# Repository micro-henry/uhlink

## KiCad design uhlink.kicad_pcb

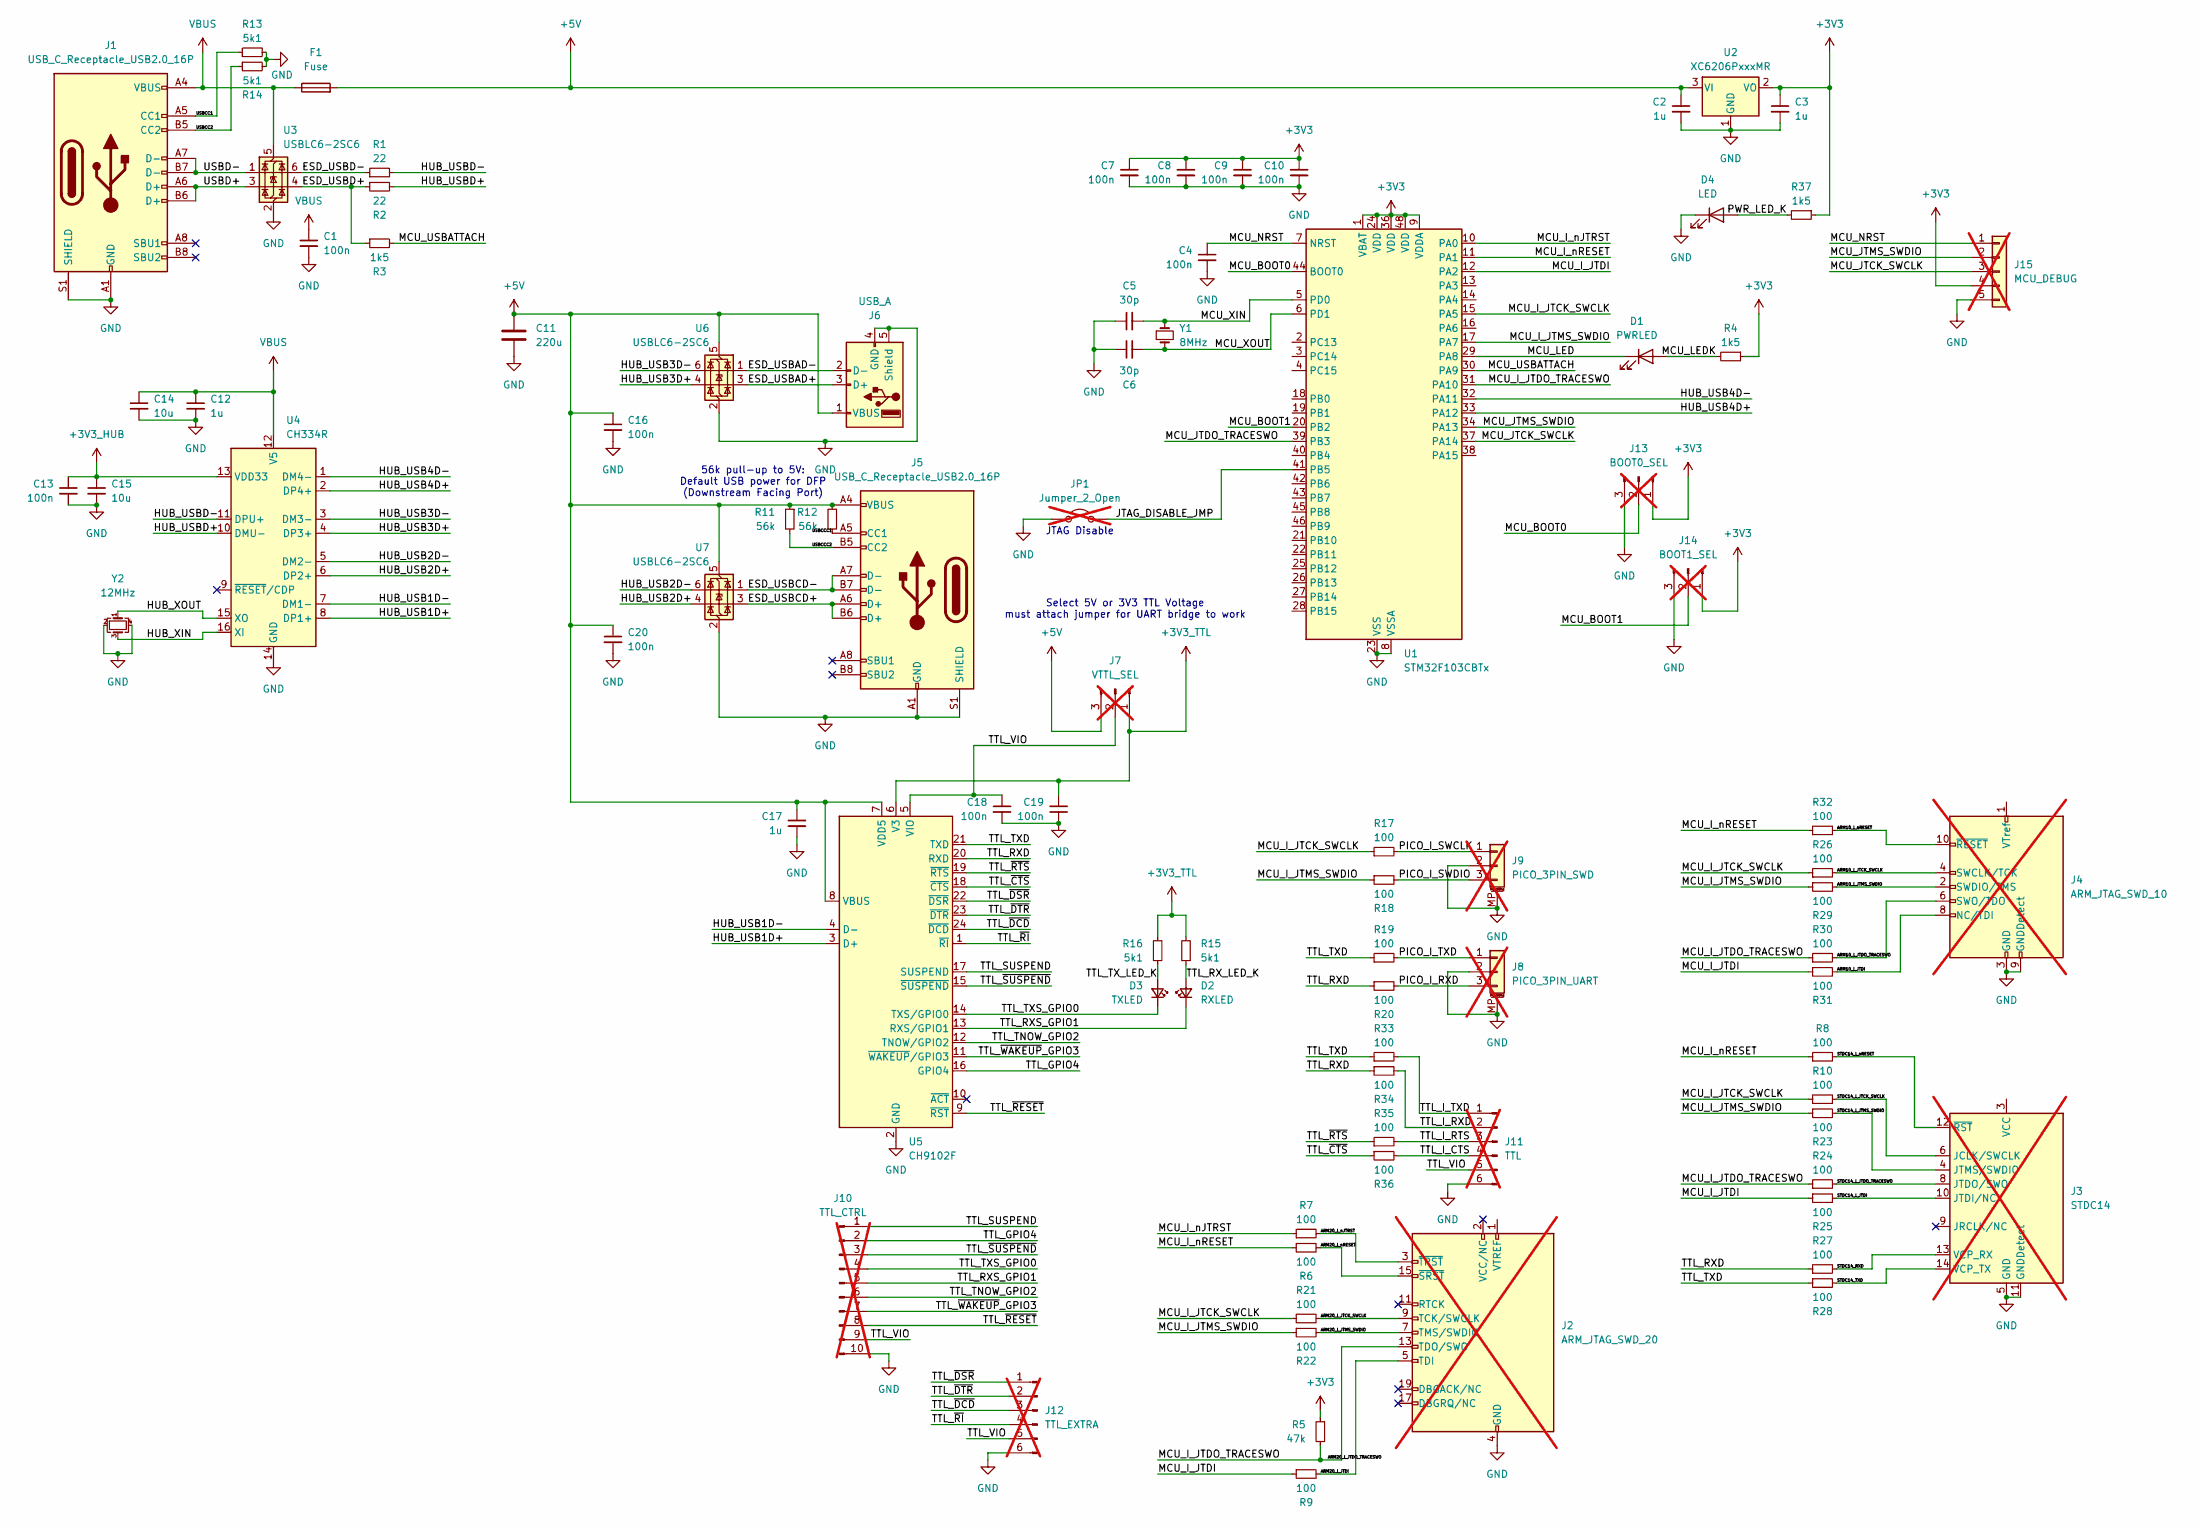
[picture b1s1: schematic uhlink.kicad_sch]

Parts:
C1, C4, C7, C8, C9, C10, C13, C16, C18, C19, C20: 100n; C_0402_1005Metric; LCSC C1525
C2, C3, C12, C17: 1u; C_0402_1005Metric; LCSC C52923
C5, C6: 30p; C_0402_1005Metric; LCSC C1570
C11: 220u; C_Radial_D10.0mm_H16.0mm_P5.00mm; LCSC C2873996
C14, C15: 10u; C_0402_1005Metric; LCSC C15525
D1: PWRLED; LED_0805_2012Metric; LCSC C84256
D2: RXLED; LED_0805_2012Metric; LCSC C2296
D3: TXLED; LED_0805_2012Metric; LCSC C2297
D4: LED; LED_0805_2012Metric; LCSC C2297
F1: Fuse
J1, J5: USB_C_Receptacle_USB2.0_16P; USB_C_Receptacle_HRO_TYPE-C-31-M-12; LCSC C2765186
J2: ARM_JTAG_SWD_20; IDC-Header_2x10_P2.54mm_Vertical; not fitted
J3: STDC14; PinHeader_2x07_P1.27mm_Vertical; not fitted
J4: ARM_JTAG_SWD_10; PinHeader_2x05_P1.27mm_Vertical; not fitted
J6: USB_A; USB_A_Receptacle_GCT_USB1046
J7: VTTL_SEL; PinHeader_1x03_P2.54mm_Vertical; not fitted
J8: PICO_3PIN_UART; JST_SH_BM03B-SRSS-TB_1x03-1MP_P1.00mm_Vertical; not fitted
J9: PICO_3PIN_SWD; JST_SH_BM03B-SRSS-TB_1x03-1MP_P1.00mm_Vertical; not fitted
J10: TTL_CTRL; PinHeader_1x10_P2.54mm_Vertical; not fitted
J11: TTL; PinHeader_1x06_P2.54mm_Vertical; not fitted
J12: TTL_EXTRA; PinHeader_1x06_P2.54mm_Vertical; not fitted
J13: BOOT0_SEL; PinHeader_1x03_P2.54mm_Vertical; not fitted
J14: BOOT1_SEL; PinHeader_1x03_P2.54mm_Vertical; not fitted
J15: MCU_DEBUG; PinHeader_1x05_P2.00mm_Vertical; not fitted
JP1: Jumper_2_Open; TestPoint_2Pads_Pitch2.54mm_Drill0.8mm; not fitted
R1, R2: 22; R_0402_1005Metric; LCSC C25092
R3, R4, R37: 1k5; R_0402_1005Metric; LCSC C25867
R5: 47k; R_0402_1005Metric; LCSC C25792
R6, R7, R8, R9, R10, R17, R18, R19, R20, R21, R22, R23, R24, R25, R26, R27, R28, R29, R30, R31, R32, R33, R34, R35, R36: 100; R_0402_1005Metric; LCSC C25076
R11, R12: 56k; R_0603_1608Metric; LCSC C23206
R13, R14, R15, R16: 5k1; R_0402_1005Metric; LCSC C25905
U1: STM32F103CBTx; LQFP-48_7x7mm_P0.5mm; LCSC C8304
U2: XC6206PxxxMR; SOT-23-3; LCSC C5446
U3, U6, U7: USBLC6-2SC6; SOT-23-6; LCSC C7519
U4: CH334R; QSOP-16_3.9x4.9mm_P0.635mm; LCSC C4154405
U5: CH9102F; QFN-24-1EP_4x4mm_P0.5mm_EP2.6x2.6mm; LCSC C2858418
Y1: 8MHz; Crystal_SMD_HC49-SD; LCSC C12674
Y2: 12MHz; Crystal_SMD_3225-4Pin_3.2x2.5mm; LCSC C9002

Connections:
+3V3: C3.1, C7.1, C8.1, C9.1, C10.1, J13.1, J14.1, J15.4, R4.1, R5.1, R37.1, U1.1 (VBAT), U1.9 (VDDA), U1.24 (VDD), U1.36 (VDD), U1.48 (VDD), U2.2 (VO)
+3V3_HUB: C13.1, C15.1, U4.13 (VDD33)
+3V3_TTL: C19.1, J7.1, R15.2, R16.2, U5.6 (V3)
+5V: C2.1, C11.1, C16.1, C17.1, C20.1, F1.2, J5.A4 (VBUS), J5.A9 (VBUS), J5.B4 (VBUS), J5.B9 (VBUS), J6.1 (VBUS), J7.3, R11.1, R12.1, U2.3 (VI), U5.7 (VDD5), U5.8 (VBUS), U6.5 (VBUS), U7.5 (VBUS)
/ARM10_I_JTCK_SWCLK: J4.4 (SWCLK/TCK), R26.2
/ARM10_I_JTDI: J4.8 (NC/TDI), R31.2
/ARM10_I_JTDO_TRACESWO: J4.6 (SWO/TDO), R30.2
/ARM10_I_JTMS_SWDIO: J4.2 (SWDIO/TMS), R29.2
/ARM10_I_nRESET: J4.10 (~RESET), R32.2
/ARM20_I_JTCK_SWCLK: J2.9 (TCK/SWCLK), R21.2
/ARM20_I_JTDI: J2.5 (TDI), R9.2
/ARM20_I_JTDO_TRACESWO: J2.13 (TDO/SWO), R5.2, R24.1, R30.1, U1.31 (PA10)
/ARM20_I_JTMS_SWDIO: J2.7 (TMS/SWDIO), R22.2
/ARM20_I_nJTRST: J2.3 (~TRST), R7.2
/ARM20_I_nRESET: J2.15 (~SRST), R6.2
/ESD_USBAD+: J6.3 (D+), U6.3 (I/O2)
/ESD_USBAD-: J6.2 (D-), U6.1 (I/O1)
/ESD_USBCD+: J5.A6 (D+), J5.B6 (D+), U7.3 (I/O2)
/ESD_USBCD-: J5.A7 (D-), J5.B7 (D-), U7.1 (I/O1)
/ESD_USBD+: R2.1, R3.1, U3.4 (I/O2)
/ESD_USBD-: R1.1, U3.6 (I/O1)
/HUB_USB1D+: U4.8 (DP1+), U5.3 (D+)
/HUB_USB1D-: U4.7 (DM1-), U5.4 (D-)
/HUB_USB2D+: U4.6 (DP2+), U7.4 (I/O2)
/HUB_USB2D-: U4.5 (DM2-), U7.6 (I/O1)
/HUB_USB3D+: U4.4 (DP3+), U6.4 (I/O2)
/HUB_USB3D-: U4.3 (DM3-), U6.6 (I/O1)
/HUB_USB4D+: U1.33 (PA12), U4.2 (DP4+)
/HUB_USB4D-: U1.32 (PA11), U4.1 (DM4-)
/HUB_USBD+: R2.2, U4.10 (DMU-)
/HUB_USBD-: R1.2, U4.11 (DPU+)
/HUB_XIN: U4.16 (XI), Y2.3
/HUB_XOUT: U4.15 (XO), Y2.1
/JTAG_DISABLE_JMP: JP1.2 (B), U1.41 (PB5)
/MCU_BOOT0: J13.2, U1.44 (BOOT0)
/MCU_BOOT1: J14.2, U1.20 (PB2)
/MCU_I_JTCK_SWCLK: R10.1, R17.1, R21.1, R26.1, U1.15 (PA5)
/MCU_I_JTDI: R9.1, R25.1, R31.1, U1.12 (PA2)
/MCU_I_JTMS_SWDIO: R18.1, R22.1, R23.1, R29.1, U1.17 (PA7)
/MCU_I_nJTRST: R7.1, U1.10 (PA0)
/MCU_I_nRESET: R6.1, R8.1, R32.1, U1.11 (PA1)
/MCU_JTCK_SWCLK: J15.3, U1.37 (PA14)
/MCU_JTDO_TRACESWO: U1.39 (PB3)
/MCU_JTMS_SWDIO: J15.2, U1.34 (PA13)
/MCU_LED: D1.1 (K), U1.29 (PA8)
/MCU_LEDK: D1.2 (A), R4.2
/MCU_NRST: C4.1, J15.1, U1.7 (NRST)
/MCU_USBATTACH: R3.2, U1.30 (PA9)
/MCU_XIN: C5.2, U1.5 (PD0), Y1.1
/MCU_XOUT: C6.2, U1.6 (PD1), Y1.2
/PICO_I_RXD: J8.3, R20.2
/PICO_I_SWCLK: J9.1, R17.2
/PICO_I_SWDIO: J9.3, R18.2
/PICO_I_TXD: J8.1, R19.2
/PWR_LED_K: D4.2 (A), R37.2
/STDC14_I_JTCK_SWCLK: J3.6 (JCLK/SWCLK), R10.2
/STDC14_I_JTDI: J3.10 (JTDI/NC), R25.2
/STDC14_I_JTDO_TRACESWO: J3.8 (JTDO/SWO), R24.2
/STDC14_I_JTMS_SWDIO: J3.4 (JTMS/SWDIO), R23.2
/STDC14_I_nRESET: J3.12 (~RST), R8.2
/STDC14_RXD: J3.13 (VCP_RX), R27.2
/STDC14_TXD: J3.14 (VCP_TX), R28.2
/TTL_GPIO4: J10.2, U5.16 (GPIO4)
/TTL_I_CTS: J11.4, R36.2
/TTL_I_RTS: J11.3, R35.2
/TTL_I_RXD: J11.2, R34.2
/TTL_I_TXD: J11.1, R33.2
/TTL_RXD: R20.1, R27.1, R34.1, U5.20 (RXD)
/TTL_RXS_GPIO1: D2.1 (K), J10.5, U5.13 (RXS/GPIO1)
/TTL_RX_LED_K: D2.2 (A), R15.1
/TTL_SUSPEND: J10.1, U5.17 (SUSPEND)
/TTL_TNOW_GPIO2: J10.6, U5.12 (TNOW/GPIO2)
/TTL_TXD: R19.1, R28.1, R33.1, U5.21 (TXD)
/TTL_TXS_GPIO0: D3.1 (K), J10.4, U5.14 (TXS/GPIO0)
/TTL_TX_LED_K: D3.2 (A), R16.1
/TTL_VIO: C18.1, J7.2, J10.9, J11.5, J12.5, U5.5 (VIO)
/TTL_~CTS: R36.1, U5.18 (~CTS)
/TTL_~DCD: J12.3, U5.24 (~DCD)
/TTL_~DSR: J12.1, U5.22 (~DSR)
/TTL_~DTR: J12.2, U5.23 (~DTR)
/TTL_~RESET: J10.8, U5.9 (~RST)
/TTL_~RI: J12.4, U5.1 (~RI)
/TTL_~RTS: R35.1, U5.19 (~RTS)
/TTL_~SUSPEND: J10.3, U5.15 (~SUSPEND)
/TTL_~WAKEUP_GPIO3: J10.7, U5.11 (~WAKEUP/GPIO3)
/USBCC1: J1.A5 (CC1), R13.1
/USBCC2: J1.B5 (CC2), R14.1
/USBCCC1: J5.A5 (CC1), R12.2
/USBCCC2: J5.B5 (CC2), R11.2
/USBD+: J1.A6 (D+), J1.B6 (D+), U3.3 (I/O2)
/USBD-: J1.A7 (D-), J1.B7 (D-), U3.1 (I/O1)
GND: C1.2, C2.2, C3.2, C4.2, C5.1, C6.1, C7.2, C8.2, C9.2, C10.2, C11.2, C12.2, C13.2, C14.2, C15.2, C16.2, C17.2, C18.2, C19.2, C20.2, D4.1 (K), J1.A1 (GND), J1.A12 (GND), J1.B1 (GND), J1.B12 (GND), J1.S1 (SHIELD), J2.4 (GND), J2.6 (GND), J2.8 (GND), J2.10 (GND), J2.12 (GND), J2.14 (GND), J2.16 (GND), J2.18 (GND), J2.20 (GND), J3.5 (GND), J3.7 (GND), J3.11 (GNDDetect), J4.3 (GND), J4.5 (GND), J4.9 (GNDDetect), J5.A1 (GND), J5.A12 (GND), J5.B1 (GND), J5.B12 (GND), J5.S1 (SHIELD), J6.4 (GND), J6.5 (Shield), J8.2, J8.MP (MountPin), J9.2, J9.MP (MountPin), J10.10, J11.6, J12.6, J13.3, J14.3, J15.5, JP1.1 (A), R13.2, R14.2, U1.8 (VSSA), U1.23 (VSS), U1.35 (VSS), U1.47 (VSS), U2.1 (GND), U3.2 (GND), U4.14 (GND), U5.2 (GND), U5.25 (GND), U6.2 (GND), U7.2 (GND), Y2.2, Y2.4
VBUS: C1.1, C12.1, C14.1, F1.1, J1.A4 (VBUS), J1.A9 (VBUS), J1.B4 (VBUS), J1.B9 (VBUS), U3.5 (VBUS), U4.12 (V5)

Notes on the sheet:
Select 5V or 3V3 TTL Voltage must attach jumper for UART bridge to work
56k pull-up to 5V: Default USB power for DFP (Downstream Facing Port)
JTAG Disable

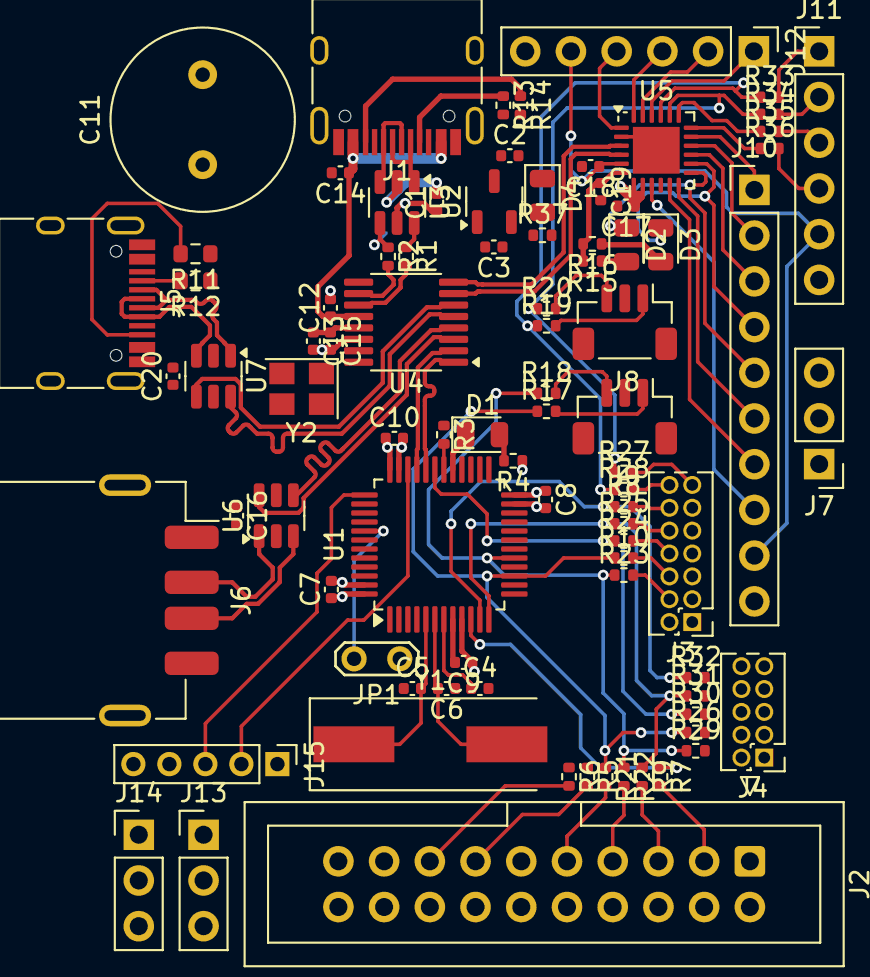
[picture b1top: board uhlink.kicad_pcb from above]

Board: 4 copper layers, 86 parts (0 on the bottom side), 92 nets.

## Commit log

2024-05-22 init: basic schematics
2024-05-22 feat: reannoate schematic, add pwr led
2024-05-22 feat: net classes+schematic colors, net labels
2024-05-22 feat: pre-layoutand adjustments
2024-05-23 feat: basic layout
